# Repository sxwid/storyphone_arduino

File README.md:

# storyphone Arduino Shield
Wählscheibentelefon MP3 Player

Code und Hardware für ein Arduino Shield. Funktionen und Details:
- Speisung 24VDC (Ein 6W Netzteil reicht)
- Schaltregler um 5V für das MP3 Modul und 9V für den Arduino VIN zu generieren (getrennt wegen Störungen des MP3 Moduls)
- Ausgabe Leitungston über DIO2
- Detektion der Gabelzustände und Wählimpulse über Optokoppler und DIO4
- USB Stick (FAT32) mit Dateien im Rootfolder:
  - 0001.mp3 für Zahl 1
  - 0002.mp3 für Zahl 2 
  -  etc 
  - 0009.mp3 für Zahl 9
  - 0010.mp3 für Zahl 0
- Volume der Audiowiedergabe kann am Drehknopf eingestellt werden

!!! Funktioniert bei mir nur mit einem Original Arduino (mit Klon bei Speisung über VIN erst nach manuellem Drücken des Reset Buttons).

Hier noch das Schema für die Autophon Geräte

Bei Standardkabelbelegung gilt:
- a Draht weiss (a)
- b Draht blau (b) 
- c Draht türkis (Wecker)
- d Draht violett

Da wir den Wecker nicht benötigen können der weisse und der blaue Draht verwendet werden.

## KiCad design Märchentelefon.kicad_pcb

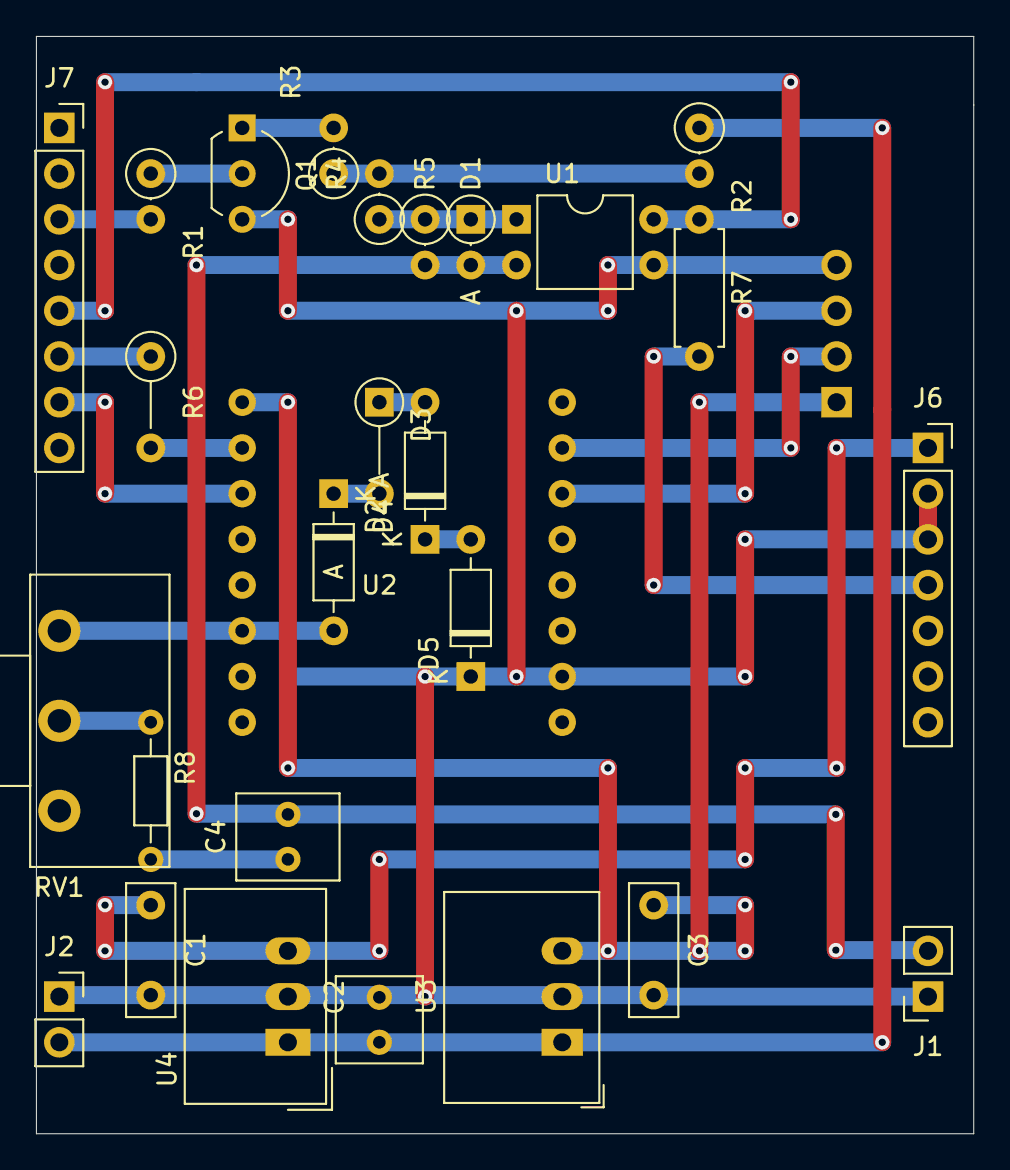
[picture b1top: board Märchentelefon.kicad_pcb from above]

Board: 2 copper layers, 52.1 x 61.0 mm, 28 parts (1 on the bottom side), 23 nets.

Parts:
C1, C3: 100n; C_Rect_L7.2mm_W2.5mm_P5.00mm_FKS2_FKP2_MKS2_MKP2
C2: 1u; C_Rect_L4.6mm_W4.6mm_P2.50mm_MKS02_FKP02
C4: 1u; C_Rect_L4.6mm_W5.5mm_P2.50mm_MKS02_FKP02
D1: 1N4148; D_DO-35_SOD27_P2.54mm_Vertical_AnodeUp
D2, D4, D5: 1N4148; D_DO-35_SOD27_P7.62mm_Horizontal
D3: 1N4148; D_DO-35_SOD27_P5.08mm_Vertical_AnodeUp
J1: Phone AB; PinSocket_1x02_P2.54mm_Vertical
J2: 24VDC; PinSocket_1x02_P2.54mm_Vertical
J3: USB_A; PinHeader_1x04_P2.54mm_Horizontal
J6: Voltage; PinSocket_1x07_P2.54mm_Vertical
J7: Digital; PinSocket_1x08_P2.54mm_Vertical
Q1: BC550; TO-92L_Inline_Wide
R1: 100k; R_Axial_DIN0207_L6.3mm_D2.5mm_P2.54mm_Vertical
R2: 330R; R_Axial_DIN0207_L6.3mm_D2.5mm_P2.54mm_Vertical
R3: 15k 1W; R_Axial_DIN0207_L6.3mm_D2.5mm_P2.54mm_Vertical
R4: 100R; R_Axial_DIN0207_L6.3mm_D2.5mm_P2.54mm_Vertical
R5: 180R; R_Axial_DIN0207_L6.3mm_D2.5mm_P2.54mm_Vertical
R6: 1k; R_Axial_DIN0207_L6.3mm_D2.5mm_P5.08mm_Vertical
R7: 100k; R_Axial_DIN0207_L6.3mm_D2.5mm_P7.62mm_Horizontal
R8: 560R; R_Axial_DIN0204_L3.6mm_D1.6mm_P7.62mm_Horizontal
RV1: 4k7; Potentiometer_Piher_T-16H_Single_Horizontal
U1: KB817; DIP-4_W7.62mm
U2: DFPlayerMini; DFPlayer_V2
U3: R-78E5.0-0.5; Converter_DCDC_RECOM_R-78E-0.5_THT
U4: TSR_1-2490; Converter_DCDC_TRACO_TSR-1_THT

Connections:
5V: J6.4, R7.2
9V: C1.1, J6.1, U4.3
24V: C2.1, J2.2, R2.1, U3.1, U4.1
DF_5V: C3.1, J3.1, U2.1, U3.3
GND: C1.2, C2.2, C3.2, D5.1, J1.1, J2.1, J3.4, J6.2, J6.3, Q1.3, U1.3, U2.10, U3.2, U4.2
I_FORK1: J7.5, R7.1, U1.4
unnamed: C4.1, R8.2
unnamed: C4.2, D1.2, J1.2, R5.2, U1.2
unnamed: D1.1, R4.1, R5.1, U1.1
unnamed: D2.1, D3.2
unnamed: D2.2, RV1.1, U2.6
unnamed: D3.1, D4.2
unnamed: D4.1, D5.2
unnamed: J3.2, U2.15
unnamed: J3.3, U2.14
unnamed: Q1.1, R3.2
unnamed: Q1.2, R1.1
unnamed: R2.2, R3.1, R4.2
unnamed: R6.2, U2.2
unnamed: R8.1, RV1.2
O_STATE: J7.3, R1.2
Player_RX: J7.6, R6.1
Player_TX: J7.7, U2.3

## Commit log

2020-08-02 Update Basic_Telefon_Functions.ino
    An Schema angepasst (Pinbelegung)
2020-08-06 Schema Autophon
